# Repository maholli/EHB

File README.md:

# EHB
Energy Harvester Board

Designed around the TI BQ25570. See short write-up here: [Flexible Energy Harvesting](https://maholli.com/Flexible-Energy-Harvesting-d48ef8ed442f40c983688aa523d03555)

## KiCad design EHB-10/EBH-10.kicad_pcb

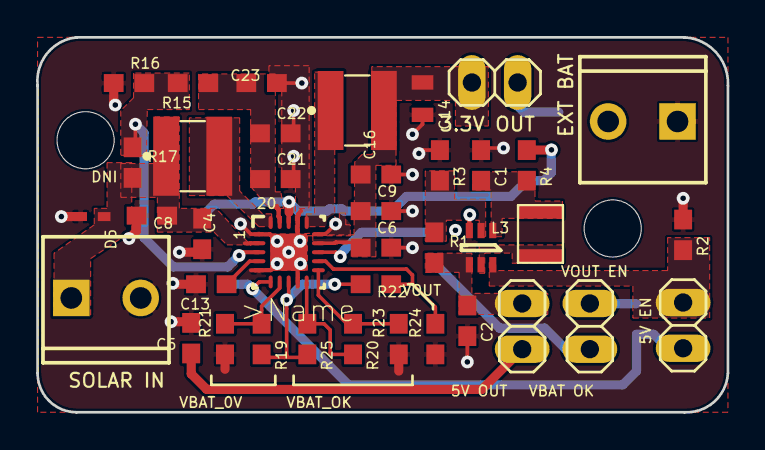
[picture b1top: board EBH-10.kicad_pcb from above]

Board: 2 copper layers, 38.4 x 20.8 mm, 49 parts (0 on the bottom side), 26 nets.

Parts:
@HOLE0, @HOLE1: (no value)
C1, C2: 10uF; 0603
C4, C21: 4.7uF; 0603
C5, C6, C8, C17, C22: 0.1uF; 0603
C9, C16, C19, C23: 100uF; 0603
C13: 10nF; 0603
C14: 22uF; 0805
C15: 1.0uF; 0603
D5: BZT52C4V7t; SOD523
FRAME1: FRAME-LETTERNO_PACKAGE; DUMMY
G2: 10MM_SM_COIN_CELL_CLIP
JP1, JP2, JP3, JP6: PINHD-1X2; 1X02
JP5, JP11: M023.5MM_LOCK; SCREWTERMINAL-3.5MM-2_LOCK
L1: 22uH-LPS4018-223MR; LPS4018
L3: 4.7uH - EPL3015-472ML; DFE322512C
L4: 10uH-LPS4018-103MR; LPS4018
R1, R2: 1M; 0603
R3: 110K; 0603
R4, R6, R7, R14, R15, R16, R17: 0; 0603
R19: 7.32M; 0603
R20, R22: 8.25M; 0603
R21: 5.62M; 0603
R23: 4.53M; 0603
R24: 4.75M; 0603
R25: 374K; 0603
U1: Value; RGR0020A
U2: TPS61220DCKR; DCK0006A

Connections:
/+3.3V: C17.1, JP3.2
/+5V: C5.1, JP1.2
/VBAT: C19.1, R4.1, R14.2, U1.18
/VBAT_OK: R6.2, U1.13
/VOUT_EN: C15.1, JP2.1, R7.2, U1.6
GND: C1.1, C2.2, C4.2, C5.2, C6.2, C8.2, C9.2, C13.2, C14.2, C15.2, C16.2, C17.2, C19.2, C21.2, C22.2, C23.2, D5.A, G2.-, JP5.1, JP11.2, R2.1, R3.1, R16.1, R21.1, R23.1, R24.1, U1.1, U1.5, U1.9, U1.15, U1.17, U1.21, U1.V, U2.3
unnamed: C1.2, L3.P$1, R4.2, U2.1
unnamed: C2.1, JP1.1, R1.2, U2.4
unnamed: C4.1, C8.1, D5.C, JP11.1, L1.1, R17.2, U1.2
unnamed: C13.1, U1.4
unnamed: C6.1, C9.1, C14.1, C16.1, JP3.1, L4.2, U1.14
unnamed: C21.1, C22.1, C23.1, R15.1, U1.19
unnamed: G2.+@1, G2.+@2, JP5.2, R14.1
unnamed: JP2.2, R2.2, U2.6
unnamed: JP6.1, R6.1
unnamed: JP6.2, R7.1
unnamed: L1.2, U1.20
unnamed: L3.P$2, U2.5
unnamed: L4.1, U1.16
unnamed: R1.1, R3.2, U2.2
unnamed: R15.2, R16.2, R17.1, U1.3
unnamed: R19.1, R21.2, U1.7
unnamed: R19.2, R22.2, R25.2, U1.8
unnamed: R20.1, R23.2, U1.11
unnamed: R20.2, R25.1, U1.10
unnamed: R22.1, R24.2, U1.12

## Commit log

2019-10-18 adding inital EHB design (already ported to kicad)
2019-10-20 schematic cleanup and adding pdf
